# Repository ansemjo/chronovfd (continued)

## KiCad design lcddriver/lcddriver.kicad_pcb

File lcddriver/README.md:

# lcddriver

This isn't entirely my own design and is instead heavily based on David Johnson-Davies' ["Low-Power LCD Clock" design on Technoblogy](http://www.technoblogy.com/show?19K8) (archived: [page](https://archive.ph/uYsL3), [firmware](https://archive.ph/4itl0)). This was created shortly after the `vfddriver` v2 and was meant to use the same physical format and I2C protocol to be a drop-in replacement. In practice, I haven't really bothered to write a separate firmware and used it as a standalone clock with David's firmware instead.

It just needed a few small modifications from the original:

* Only `PE0` is connected to the display's `COM`. `PE1` is used for an LED and if you use the firmware as-is, you'll have a constantly flashing LED.

* I used an **AVR32DB48** and apparently (?) it lacks some of the ADC stuff necessary to read its own voltage? So I just removed `ADCSetup()`, `DisplayVoltage()` and the references to it.

* Additionally, I removed the temperature display and reduced the blinking frequency of the colon by to 2 Hz.

There is also an inverted variant of the firmware, for when you want to operate the clock rotated by 180°, since the LCD segments are rotationally symmetric but the viewing angle is better from one side.

### Compile

The firmware is in `technoblogy-clock-firmware/`.

The chip [is supported](https://docs.platformio.org/en/latest/boards/atmelmegaavr/AVR32DB48.html) by PlatformIO but back when I tried this, I couldn't get it to work. I got either `Error: Unknown board ID 'AVR32DB48'` or `Error: This board doesn't support Arduino framework!`. Therefore I used the method that David used and installed the [DxCore](https://github.com/SpenceKonde/DxCore) in the Arduino IDE, which I then used to compile the firmware instead.

### Flashing

For some reason the Arduino GUI couldn't directly flash my chip. Probably something about a wrong Python version. I manually installed [`pymcuprog`](https://pypi.org/project/pymcuprog/) in a Python 3.9.12 environment and used:

```
pymcuprog write -d avr32db48 -t uart -u /dev/ttyUSB1 -f lcdclock.ino.hex
```

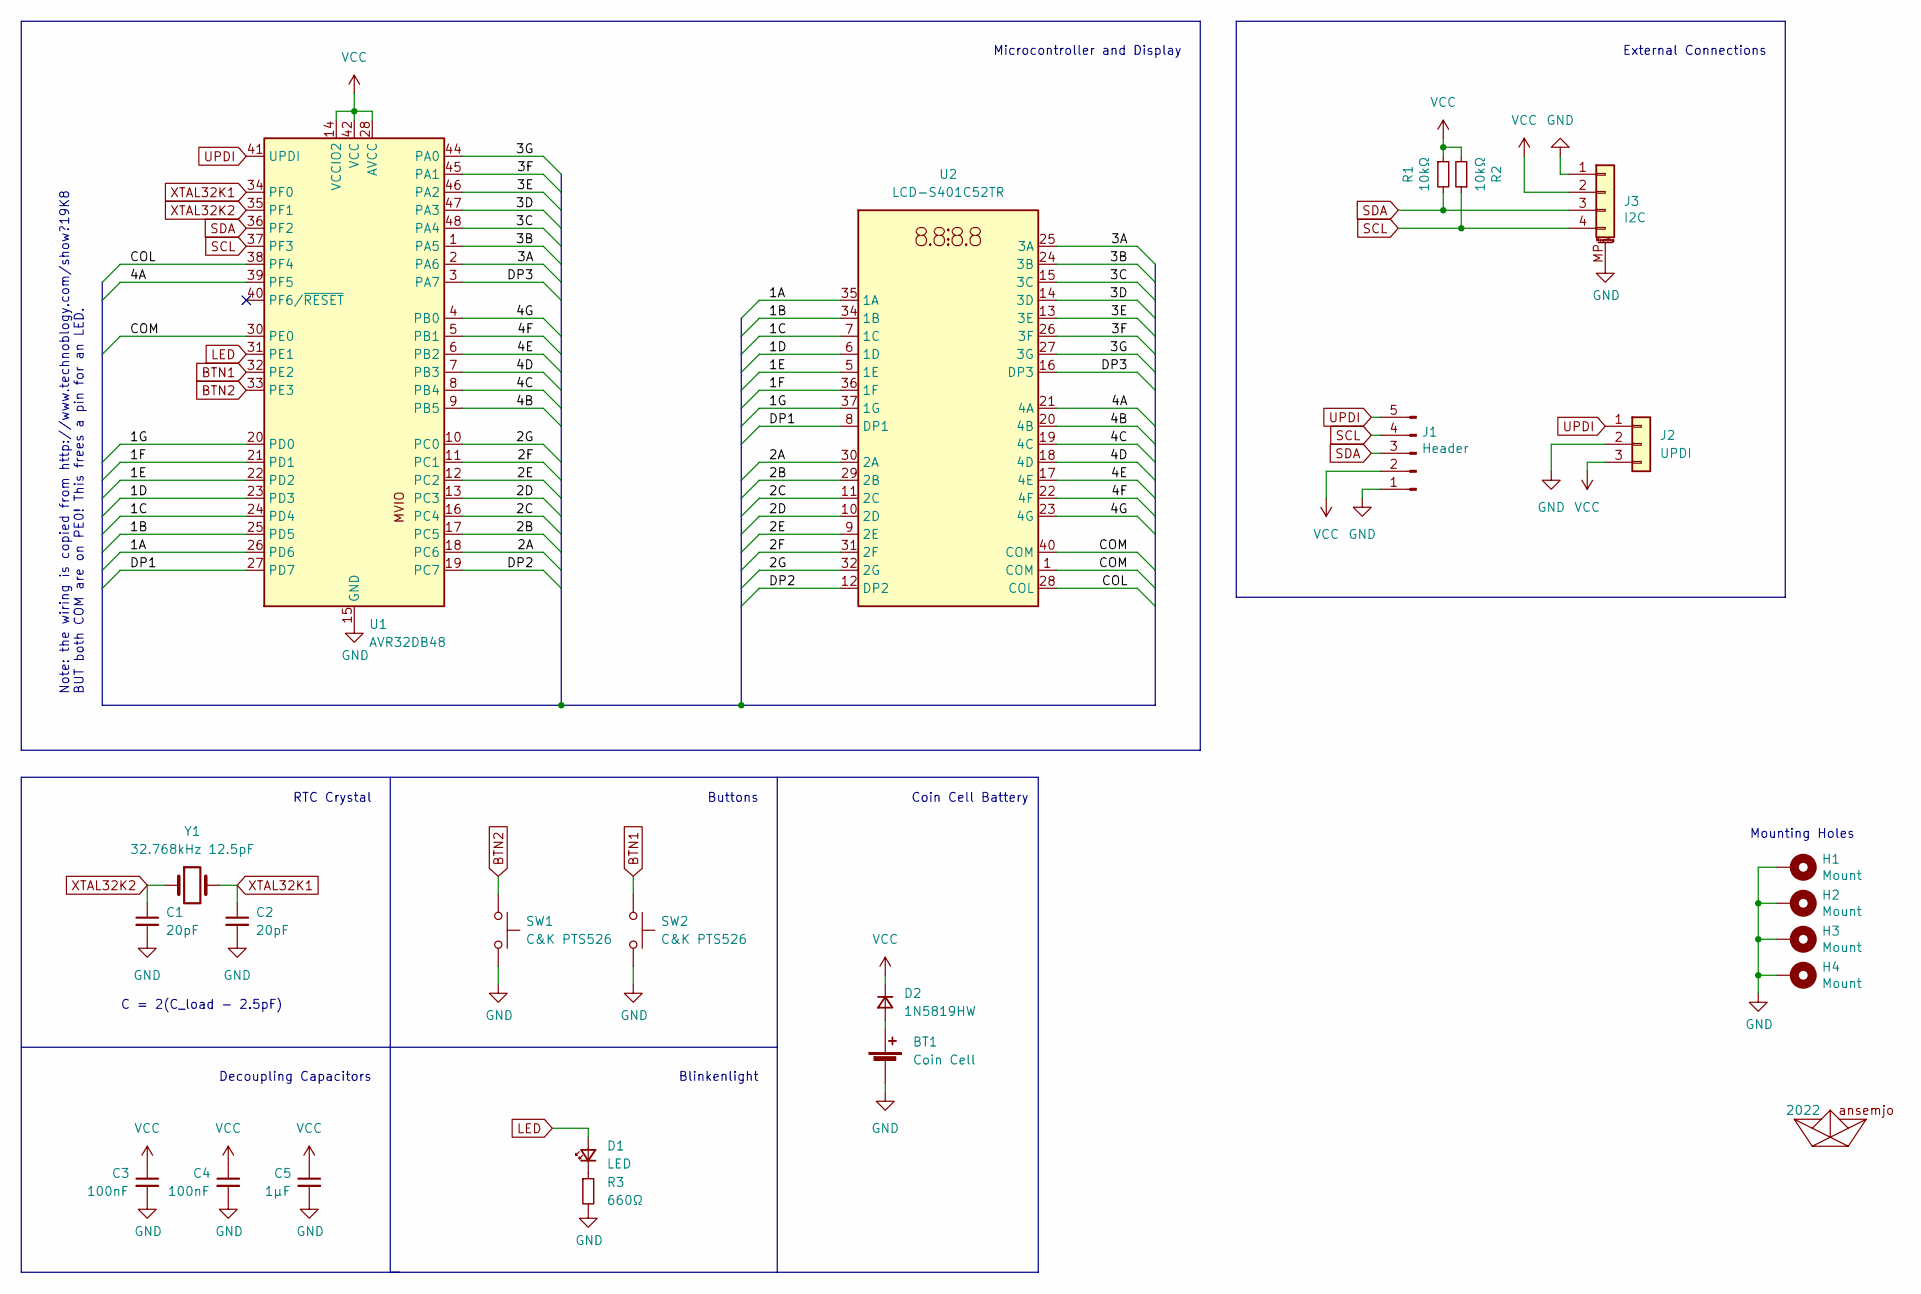
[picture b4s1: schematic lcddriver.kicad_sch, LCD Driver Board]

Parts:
A1: 2022; ahoi
BT1: Coin Cell; BatteryHolder_Keystone_3034_1x20mm
C1, C2: 20pF; C_0603_1608Metric_Pad1.08x0.95mm_HandSolder
C3, C4: 100nF; C_0805_2012Metric_Pad1.18x1.45mm_HandSolder; MPN UMK212BBJ475KG-T; Digi-Key PN 587-5485-1-ND
C5: 1µF; C_0805_2012Metric_Pad1.18x1.45mm_HandSolder; MPN UMK212BBJ475KG-T; Digi-Key PN 587-5485-1-ND
D1: LED; LED_0805_2012Metric_Pad1.15x1.40mm_HandSolder
D2: 1N5819HW; D_SOD-123
H1, H2, H3, H4: Mount; MountingHole_2.7mm_M2.5_Pad
J1: Header; PinHeader_1x05_P2.54mm_Vertical; MPN PREC040DBAN-M71RC; Digi-Key PN S2112EC-40-ND
J2: UPDI; UPDI_PogoProg
J3: I2C; JST_SH_SM04B-SRSS-TB_1x04-1MP_P1.00mm_Horizontal
R1, R2: 10kΩ; R_0805_2012Metric_Pad1.20x1.40mm_HandSolder; MPN RC0805FR-0710KL; Digi-Key PN 311-10.0KCRCT-ND
R3: 660Ω; R_0805_2012Metric_Pad1.20x1.40mm_HandSolder
SW1, SW2: C&K PTS526; SW_PTS526_SM08_SMTR2_LFS
U1: AVR32DB48; TQFP-48_7x7mm_P0.5mm
U2: LCD-S401C52TR; DE119-XX-XX
Y1: 32.768kHz 12.5pF; Crystal_SMD_3215-2Pin_3.2x1.5mm

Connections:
/1A: U1.26 (PD6), U2.35 (1A)
/1B: U1.25 (PD5), U2.34 (1B)
/1C: U1.24 (PD4), U2.7 (1C)
/1D: U1.23 (PD3), U2.6 (1D)
/1E: U1.22 (PD2), U2.5 (1E)
/1F: U1.21 (PD1), U2.36 (1F)
/1G: U1.20 (PD0), U2.37 (1G)
/2A: U1.18 (PC6), U2.30 (2A)
/2B: U1.17 (PC5), U2.29 (2B)
/2C: U1.16 (PC4), U2.11 (2C)
/2D: U1.13 (PC3), U2.10 (2D)
/2E: U1.12 (PC2), U2.9 (2E)
/2F: U1.11 (PC1), U2.31 (2F)
/2G: U1.10 (PC0), U2.32 (2G)
/3A: U1.2 (PA6), U2.25 (3A)
/3B: U1.1 (PA5), U2.24 (3B)
/3C: U1.48 (PA4), U2.15 (3C)
/3D: U1.47 (PA3), U2.14 (3D)
/3E: U1.46 (PA2), U2.13 (3E)
/3F: U1.45 (PA1), U2.26 (3F)
/3G: U1.44 (PA0), U2.27 (3G)
/4A: U1.39 (PF5), U2.21 (4A)
/4B: U1.9 (PB5), U2.20 (4B)
/4C: U1.8 (PB4), U2.19 (4C)
/4D: U1.7 (PB3), U2.18 (4D)
/4E: U1.6 (PB2), U2.17 (4E)
/4F: U1.5 (PB1), U2.22 (4F)
/4G: U1.4 (PB0), U2.23 (4G)
/COL: U1.38 (PF4), U2.28 (COL)
/COM: U1.30 (PE0), U2.1 (COM), U2.40 (COM)
/DP1: U1.27 (PD7), U2.8 (DP1)
/DP2: U1.19 (PC7), U2.12 (DP2)
/DP3: U1.3 (PA7), U2.16 (DP3)
BTN1: SW2.1, U1.32 (PE2)
BTN2: SW1.1, U1.33 (PE3)
GND: BT1.2 (-), C1.2, C2.2, C3.2, C4.2, C5.2, H1.1, H2.1, H3.1, H4.1, J1.1, J2.2, J3.1, J3.MP (MountPin), R3.2, SW1.2, SW2.2, U1.15 (GND), U1.29 (GND), U1.43 (GND)
LED: D1.2 (A), U1.31 (PE1)
unnamed: BT1.1 (+), D2.2 (A)
unnamed: D1.1 (K), R3.1
SCL: J1.4, J3.4, R2.1, U1.37 (PF3)
SDA: J1.3, J3.3, R1.2, U1.36 (PF2)
UPDI: J1.5, J2.1, U1.41 (UPDI)
XTAL32K1: C2.1, U1.34 (PF0), Y1.2
XTAL32K2: C1.1, U1.35 (PF1), Y1.1

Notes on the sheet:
Decoupling Capacitors
Buttons
RTC Crystal
C = 2(C_load - 2.5pF)
Blinkenlight
Coin Cell Battery
Note: the wiring is copied from http://www.technoblogy.com/show?19K8 BUT both COM are on PE0! This frees a pin for an LED.
Microcontroller and Display
Mounting Holes
External Connections

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
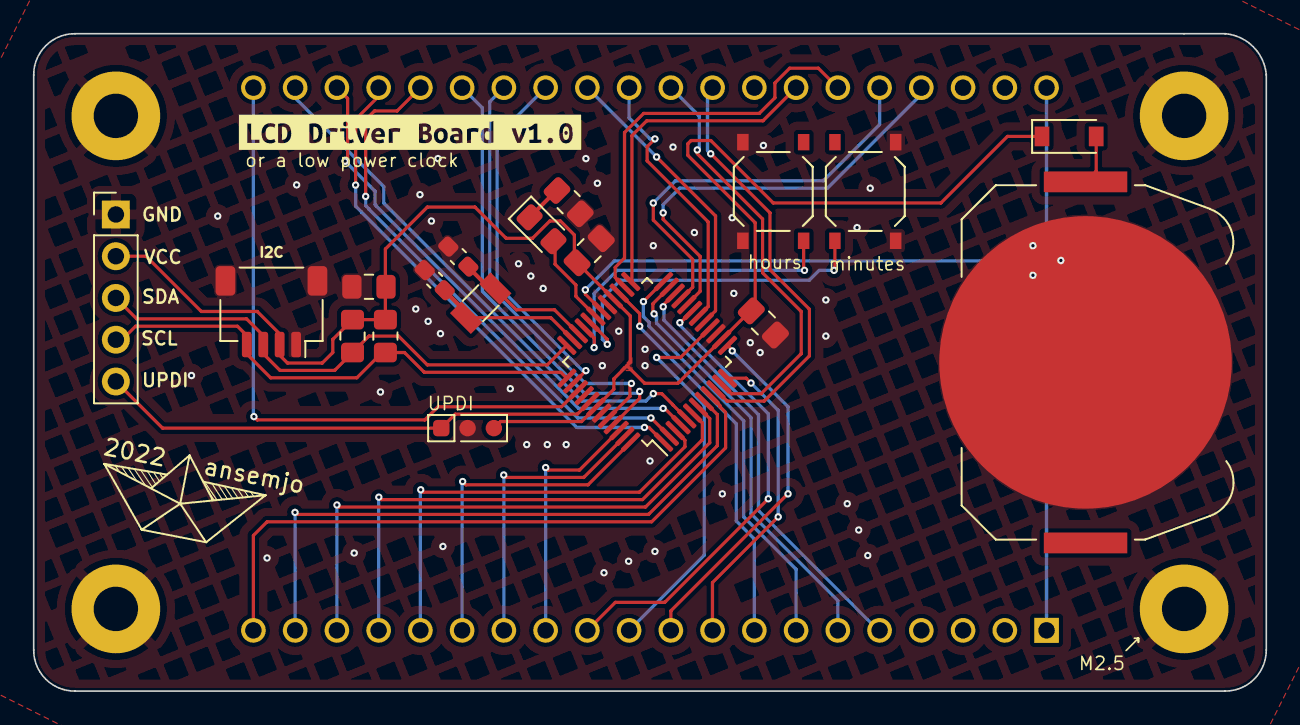
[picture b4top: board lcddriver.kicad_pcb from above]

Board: 2 copper layers, 75.0 x 40.0 mm, 25 parts (1 on the bottom side), 45 nets.

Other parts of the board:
kibuzzard-6311A385: G***; kibuzzard-6311A385

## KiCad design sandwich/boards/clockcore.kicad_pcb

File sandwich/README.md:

# chronovfd

~~ *a vacuum-flourescent display clock project* ~~

The first prototype of this clock was built completely on protoboard and can be
seen on [my Twitter](https://twitter.com/ansemjo/status/1235315817937596424).

This has become my first somewhat complex hardware project and as of now I have
assembled multiple printed circuit boards for the "display driver" and the
"clock core". After fiddling with Espressif's development framework for a while
the assembled hardware now actually works as a clock with internet time
synchronization. :)

You'll find:

* some initial research and ressources on the topic in `research/`
* [hardware](#hardware) files in `hardware/`
* the [firmware](#firmware) in a PlatformIO project in `firmware/`

# Hardware

As mentioned above the final assembly consists of two sandwiched boards:

* [VFD Driver](#vfd-driver-board)
* [Clock Core](#clock-core)

The boards were designed with KiCad version 5.1.6.

The bill-of-materials files contain Digi-Key part numbers, so you can easily
import all parts into your cart. Only the IVL2-7/5 display itself needs to be
sourced elsewhere but there are plenty on [eBay](https://www.ebay.com/sch/i.html?_nkw=ivl2-7%2F5).

Both boards can be screwed together e.g. with 11 mm M2.5 standoffs between
them. I have found some that are marketed as a "Raspberry Pi assembly kit" that
fit well.

### Errata

Sometimes things go wrong .. these are known errors and how to fix them:

* [Rev1.0: Fix the ambient light sensor photodiode](hardware/errata/rev1.0-photodiode/erratum-photodiode.md)

## VFD Driver Board

The VFD driver board is basically a power supply and a simple shift register
with a high-voltage capable output side. I used Rolo's *Universal VFD PSU*
design from [this EEVblog forum post](https://www.eevblog.com/forum/projects/showing-my-vfd-psu/).
The original [schematics](research/universal-vfd-psu/schematic_r2.1.pdf) and
a few pictures are mirrored in `research/universal-vfd-psu/`.

It can be used standalone but there is no logic on the board, so you'll have
to implement time multiplexing for the digits yourself. See the
[Microchip HV5812 datasheet](http://ww1.microchip.com/downloads/en/DeviceDoc/20005629A.pdf)
for more information. The gist is:

* supply regulated 5V power on `GND` / `5V`
* data is transmitted over `clock` and `data` with SPI mode 0 transactions at 5 MHz
* the output pin numbers are listed with their segment or grid function on the silkscreen
* toggle the `strobe` pin `HIGH` to latch the data to the high voltage outputs
* pulling the `filShdn` pin `HIGH` disables the filament supply
* pulling the `hvShdn` pin `LOW` disabled the high-voltage supply
* when the shutdown pins are left floating / in high-Z state, they are pulled active internally, so the display is "on"
* PWM dimming the brigthness with the filament shutdown pin is possible

### Design files

| type | file |
| ---- | ---- |
| kicad project | `hardware/vfddriver.pro` |
| schematic | [`hardware/vfddriver.pdf`](https://github.com/ansemjo/chronovfd/raw/master/hardware/vfddriver.pdf) |
| bill of materials | [`hardware/vfddriver_bom.csv`](hardware/vfddriver_bom.csv) |
| interactive bom | [`hardware/vfddriver_ibom.html`](https://raw.githack.com/ansemjo/chronovfd/master/hardware/vfddriver_ibom.html) |

### Images

## Clock Core

The Clock Core board is the control logic for this clock project. If you look
at the bill of materials it is a relatively expensive board for what it's
supposed to do but I wanted to experiment with some of these components. On
this board there are:

* an Espressif `ESP32-WROOM-32` module, which has WiFi and Bluetooth connectivity
* a USB 2.0 Type-C receptacle for power and data with relatively good input protections and a 3.3V linear regulator
* an FTDI `FT231XS` with an auto-reset circuit providing a serial programming and communication interface to the ESP32
* a Maxim `DS1338Z-33+` RTC with a crystal, which is connected to the ESP32 over I²C and has a coin cell battery backup
* a Maxim `DS18B20U` temperature sensor with a OneWire interface
* a footprint for a photodiode to sense ambient light levels
* a Texas Instruments `SN74HCT245PWR` level shifter to provide the correct logic levels to the VFD driver board
* a PWR and a USR LED for that blinkenlights, the PWR LED can be disabled by cutting a solder jumper
* a 10-pin 1.27mm JTAG header for the ESP32

### Design files

| type | file |
| ---- | ---- |
| kicad project | `hardware/clockcore.pro` |
| schematic | [`hardware/clockcore.pdf`](https://github.com/ansemjo/chronovfd/raw/master/hardware/clockcore.pdf) |
| bill of materials | [`hardware/clockcore_bom.csv`](hardware/clockcore_bom.csv) |
| interactive bom | [`hardware/clockcore_ibom.html`](https://raw.githack.com/ansemjo/chronovfd/master/hardware/clockcore_ibom.html) |

### Images

# Firmware

The firmware is kept in a PlatformIO project. So – if you have `platformio`
already installed – all you need to do is connect the Clock Core via USB and run:

    pio run -t upload

Generally, this board is compatible with most ESP32 devkit configurations. I'm
using a custom board definition mainly to get faster upload speeds, which the
onboard FTDI FT231X can handle. For new projects you may use `pio init -b esp32dev`.

After flashing the firmware, the board starts in **provisioning mode** and you'll
see the word `Prov` blink on the display. Use the
[ESP BLE Provisioning](https://play.google.com/store/apps/details?id=com.espressif.provble)
app to connect and provision your WiFi credentials.

**Note:** I haven't configured a *proof-of-posession* in the firmware, so you
must disable *Encrypted Device Communication* in the app settings first. If you
want to encrypt the provisioning step, look into `wireless_provision()` in
`src/wireless.c`.

Afterwards, the chip will connect to the internet and attempt to synchronize the
time. This will be written to the RTC, which will keep the time as long as an
RTC backup battery is present. If upon poweron the last synchronization is more
than two hours ago, the clock will be synchronized once immediately. Otherwise
it runs on a schedule every night at 05:00. See `src/realtimeclock.c` if you
want to change that. You should probably also fix the timezone if you're not
in the "Europe/Berlin" zone. That is set in `app_main()` with a call to `setenv()`.

# LICENSE

Unless otherwise noted in the file (`ds1307.*`, `i2cdev.*`) the firmware is licensed
under an MIT license, which can be found in [LICENSE](LICENSE).

The hardware project is licensed under a CERN Open Hardware Licence Version 2 -
Permissive, which can be found in [hardware/LICENSE](hardware/LICENSE).

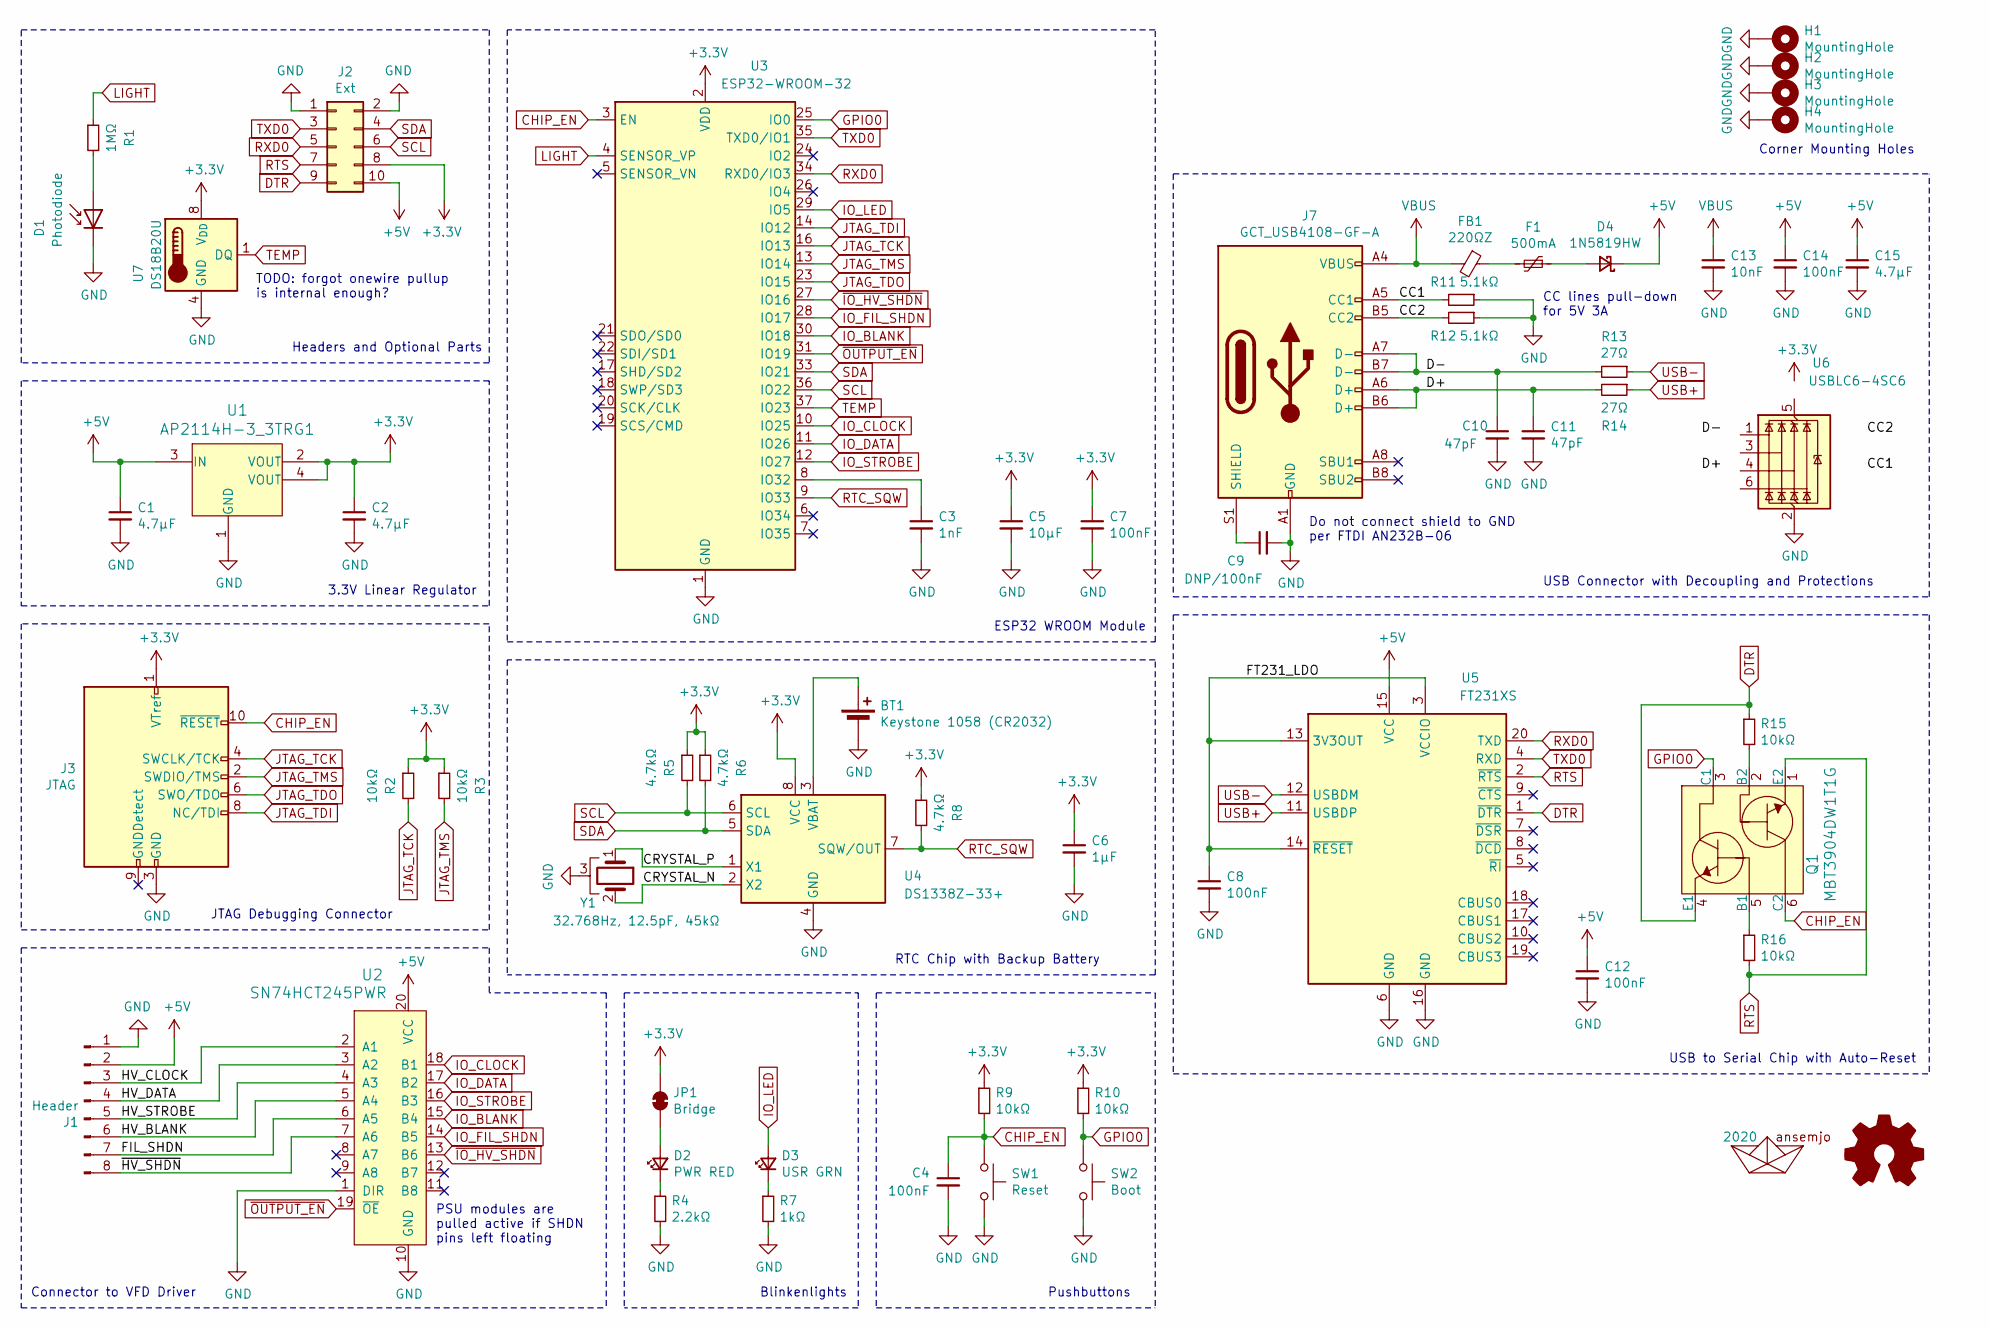
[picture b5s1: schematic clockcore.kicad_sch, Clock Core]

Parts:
A1: 2020; AHOI
A2: Logo_Open_Hardware_Small; OSHW-Symbol_6.7x6mm_SilkScreen
BT1: Keystone 1058 (CR2032); BatteryHolder_Keystone_1058_1x2032; MPN 1058; Digi-Key_PN 36-1058-ND
C1, C2, C15: 4.7µF; C_0805_2012Metric_Pad1.15x1.40mm_HandSolder; MPN CL21A475KAQNNNE; Digi-Key_PN 1276-1244-1-ND
C3: 1nF; C_0805_2012Metric_Pad1.15x1.40mm_HandSolder; MPN CL21B102KBANNNC; Digi-Key_PN 1276-1020-1-ND
C4, C7, C8, C12, C14: 100nF; C_0805_2012Metric_Pad1.15x1.40mm_HandSolder; MPN CL21B104KACNNNC; Digi-Key_PN 1276-1099-1-ND
C5: 10µF; C_0805_2012Metric_Pad1.15x1.40mm_HandSolder; MPN CL21A106KOQNNNE; Digi-Key_PN 1276-1096-1-ND
C6: 1µF; C_0805_2012Metric_Pad1.15x1.40mm_HandSolder; MPN CL21B105KAFNNNG; Digi-Key_PN 1276-6469-1-ND
C9: DNP/100nF; C_0805_2012Metric_Pad1.15x1.40mm_HandSolder; MPN CL21B104KACNNNC; Digi-Key_PN 1276-1099-1-ND
C10, C11: 47pF; C_0805_2012Metric_Pad1.15x1.40mm_HandSolder; MPN CC0805JRNPO9BN470; Digi-Key_PN 311-1107-1-ND
C13: 10nF; C_0805_2012Metric_Pad1.15x1.40mm_HandSolder; MPN CC0805KRX7R9BB103; Digi-Key_PN 311-1136-1-ND
D1: Photodiode; D_1206_3216Metric_Castellated; MPN VEMD1060X01; Digi-Key_PN VEMD1060X01CT-ND
D2: PWR RED; LED_0805_2012Metric_Pad1.15x1.40mm_HandSolder; MPN 150080SS75000; Digi-Key_PN 732-4985-1-ND
D3: USR GRN; LED_0805_2012Metric_Pad1.15x1.40mm_HandSolder; MPN 150080VS75000; Digi-Key_PN 732-4986-1-ND
D4: 1N5819HW; D_SOD-123; MPN 1N5819HW-7-F; Digi-Key_PN 1N5819HW-FDICT-ND
F1: 500mA; Fuse_1206_3216Metric_Pad1.42x1.75mm_HandSolder; MPN 0ZCJ0050FF2G; Digi-Key_PN 507-1802-1-ND
FB1: 220ΩZ; L_0805_2012Metric_Pad1.15x1.40mm_HandSolder; MPN BLM21PG221SZ1D; Digi-Key_PN 490-16661-1-ND
H1, H2, H3, H4: MountingHole; MountingHole_2.7mm_M2.5_Pad
J1: Header; PinSocket_1x08_P2.54mm_Vertical; MPN PPTC081LFBN-RC; Digi-Key_PN S7006-ND
J2: Ext; PinHeader_2x05_P2.54mm_Vertical; MPN PRPC040DAAN-RC; Digi-Key_PN S2011EC-40-ND
J3: JTAG; JTAG_2x05_P1.27mm_Vertical_SMD; MPN 20021121-00010C4LF; Digi-Key_PN 609-3695-6-ND
J7: GCT_USB4108-GF-A; USB_C_Receptacle_HRO_TYPE-C-31-M-12; MPN USB4105-GF-A; Digi-Key_PN 2073-USB4105-GF-ACT-ND
JP1: Bridge; SolderJumper-2_P1.3mm_Bridged_RoundedPad1.0x1.5mm
Q1: MBT3904DW1T1G; SOT-363; MPN MBT3904DW1T1G; Digi-Key_PN MBT3904DW1T1GOSCT-ND
R1: 1MΩ; R_0805_2012Metric_Pad1.15x1.40mm_HandSolder; MPN RC0805FR-071ML; Digi-Key_PN 311-1.00MCRCT-ND
R2, R3, R9, R10, R15, R16: 10kΩ; R_0805_2012Metric_Pad1.15x1.40mm_HandSolder; MPN RC0805FR-0710KL; Digi-Key_PN 311-10.0KCRCT-ND
R4: 2.2kΩ; R_0805_2012Metric_Pad1.15x1.40mm_HandSolder; MPN RC0805FR-072K2L; Digi-Key_PN 311-2.20KCRCT-ND
R5, R6, R8: 4.7kΩ; R_0805_2012Metric_Pad1.15x1.40mm_HandSolder; MPN RC0805FR-074K7L; Digi-Key_PN 311-4.70KCRCT-ND
R7: 1kΩ; R_0805_2012Metric_Pad1.15x1.40mm_HandSolder; MPN RC0805FR-071KL; Digi-Key_PN 311-1.00KCRCT-ND
R11, R12: 5.1kΩ; R_0805_2012Metric_Pad1.15x1.40mm_HandSolder; MPN RC0805JR-075K1L; Digi-Key_PN 311-5.1KARCT-ND
R13, R14: 27Ω; R_0805_2012Metric_Pad1.15x1.40mm_HandSolder; MPN RC0805FR-0727RL; Digi-Key_PN 311-27.0CRCT-ND
SW1: Reset; SW_PTS526_SM08_SMTR2_LFS; MPN PTS526 SK15 SMTR2 LFS; Digi-Key_PN CKN12221-1-ND
SW2: Boot; SW_PTS526_SM08_SMTR2_LFS; MPN PTS526 SK15 SMTR2 LFS; Digi-Key_PN CKN12221-1-ND
U1: AP2114H-3_3TRG1; SOT-223; MPN AP2114H-3.3TRG1; Digi-Key_PN AP2114H-3.3TRG1DICT-ND
U2: ‎SN74HCT245PWR‎; TSSOP-20_4.4x6.5mm_P0.65mm; MPN SN74HCT245PWR; Digi-Key_PN 296-8404-1-ND
U3: ESP32-WROOM-32; MPN ESP32-WROOM-32E (8MB); Digi-Key_PN 1965-ESP32-WROOM-32E(8MBFLASH)CT-ND
U4: DS1338Z-33+; SOIC-8_3.9x4.9mm_P1.27mm; MPN DS1338Z-33+T&R; Digi-Key_PN DS1338Z-33+T&RCT-ND
U5: FT231XS; SSOP-20_3.9x8.7mm_P0.635mm; MPN FT231XS-R; Digi-Key_PN 768-1129-1-ND
U6: USBLC6-4SC6; SOT-23-6; MPN USBLC6-4SC6; Digi-Key_PN 497-4492-1-ND
U7: DS18B20U; MSOP-8_3x3mm_P0.65mm; MPN DS18B20U+T&R; Digi-Key_PN DS18B20U+T&RCT-ND
Y1: 32.768Hz, 12.5pF, 45kΩ; Crystal_SMD_MicroCrystal_MS1V-T1K; MPN ECS-.327-12.5-13FLX-C; Digi-Key_PN XC1911CT-ND

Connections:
+3V3: C2.1, C5.1, C6.1, C7.1, J2.8, J3.1 (VTref), JP1.1 (A), R2.1, R3.1, R5.1, R6.1, R8.1, R9.1, R10.1, U1.2 (VOUT), U1.4 (VOUT), U3.2 (VDD), U4.8 (VCC), U6.5 (VBUS), U7.8 (V_{DD})
+5V: C1.1, C12.1, C14.1, C15.1, D4.1 (K), J1.2, J2.10, U1.3 (IN), U2.20 (VCC), U5.15 (VCC)
/CC1: J7.A5 (CC1), R11.2, U6.6 (I/O4)
/CC2: J7.B5 (CC2), R12.2, U6.4 (I/O3)
/CRYSTAL_N: U4.2 (X2), Y1.2
/CRYSTAL_P: U4.1 (X1), Y1.1
/D+: C11.1, J7.A6 (D+), J7.B6 (D+), R14.2, U6.3 (I/O2)
/D-: C10.1, J7.A7 (D-), J7.B7 (D-), R13.2, U6.1 (I/O1)
/FIL_SHDN: J1.7, U2.6 (A5)
/FT231_LDO: C8.1, U5.3 (VCCIO), U5.13 (3V3OUT), U5.14 (~RESET)
/HV_BLANK: J1.6, U2.5 (A4)
/HV_CLOCK: J1.3, U2.2 (A1)
/HV_DATA: J1.4, U2.3 (A2)
/HV_STROBE: J1.5, U2.4 (A3)
/~HV_SHDN: J1.8, U2.7 (A6)
CHIP_EN: C4.1, J3.10 (~RESET), Q1.6 (C2), R9.2, SW1.1, U3.3 (EN)
DTR: J2.9, Q1.4 (E1), R15.1, U5.1 (~DTR)
GND: BT1.2 (-), C1.2, C2.2, C3.2, C4.2, C5.2, C6.2, C7.2, C8.2, C9.2, C10.2, C11.2, C12.2, C13.2, C14.2, C15.2, D1.1 (K), H1.1, H2.1, H3.1, H4.1, J1.1, J2.1, J2.2, J3.3 (GND), J3.5 (GND), J7.A1 (GND), J7.A12 (GND), J7.B1 (GND), J7.B12 (GND), R4.2, R7.2, R11.1, R12.1, SW1.2, SW2.2, U1.1 (GND), U2.1 (DIR), U2.10 (GND), U3.1 (GND), U3.15 (GND), U3.38 (GND), U3.39 (GND), U4.4 (GND), U5.6 (GND), U5.16 (GND), U6.2 (GND), U7.4 (GND), Y1.3
GPIO0: Q1.3 (C1), R10.2, SW2.1, U3.25 (IO0)
IO_BLANK: U2.15 (B4), U3.30 (IO18)
IO_CLOCK: U2.18 (B1), U3.10 (IO25)
IO_DATA: U2.17 (B2), U3.11 (IO26)
IO_FIL_SHDN: U2.14 (B5), U3.28 (IO17)
IO_LED: D3.2 (A), U3.29 (IO5)
IO_STROBE: U2.16 (B3), U3.12 (IO27)
JTAG_TCK: J3.4 (SWCLK/TCK), R2.2, U3.16 (IO13)
JTAG_TDI: J3.8 (NC/TDI), U3.14 (IO12)
JTAG_TDO: J3.6 (SWO/TDO), U3.23 (IO15)
JTAG_TMS: J3.2 (SWDIO/TMS), R3.2, U3.13 (IO14)
LIGHT: R1.1, U3.4 (SENSOR_VP)
unnamed: BT1.1 (+), U4.3 (VBAT)
unnamed: C3.1, U3.8 (IO32)
unnamed: C9.1, J7.S1 (SHIELD)
unnamed: D1.2 (A), R1.2
unnamed: D2.1 (K), R4.1
unnamed: D2.2 (A), JP1.2 (B)
unnamed: D3.1 (K), R7.1
unnamed: D4.2 (A), F1.1
unnamed: F1.2, FB1.1
unnamed: Q1.2 (B2), R15.2
unnamed: Q1.5 (B1), R16.1
RTC_SQW: R8.2, U3.9 (IO33), U4.7 (SQW/OUT)
RTS: J2.7, Q1.1 (E2), R16.2, U5.2 (~RTS)
RXD0: J2.5, U3.34 (RXD0/IO3), U5.20 (TXD)
SCL: J2.6, R5.2, U3.36 (IO22), U4.6 (SCL)
SDA: J2.4, R6.2, U3.33 (IO21), U4.5 (SDA)
TEMP: U3.37 (IO23), U7.1 (DQ)
TXD0: J2.3, U3.35 (TXD0/IO1), U5.4 (RXD)
USB+: R14.1, U5.11 (USBDP)
USB-: R13.1, U5.12 (USBDM)
VBUS: C13.1, FB1.2, J7.A4 (VBUS), J7.A9 (VBUS), J7.B4 (VBUS), J7.B9 (VBUS)
~IO_HV_SHDN: U2.13 (B6), U3.27 (IO16)
~OUTPUT_EN: U2.19 (~OE), U3.31 (IO19)

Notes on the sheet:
Blinkenlights
TODO: forgot onewire pullup is internal enough?
Pushbuttons
Do not connect shield to GND per FTDI AN232B-06
Corner Mounting Holes
USB to Serial Chip with Auto-Reset
PSU modules are pulled active if SHDN pins left floating
USB Connector with Decoupling and Protections
Connector to VFD Driver
ESP32 WROOM Module
RTC Chip with Backup Battery
JTAG Debugging Connector
Headers and Optional Parts
3.3V Linear Regulator
CC lines pull-down for 5V 3A

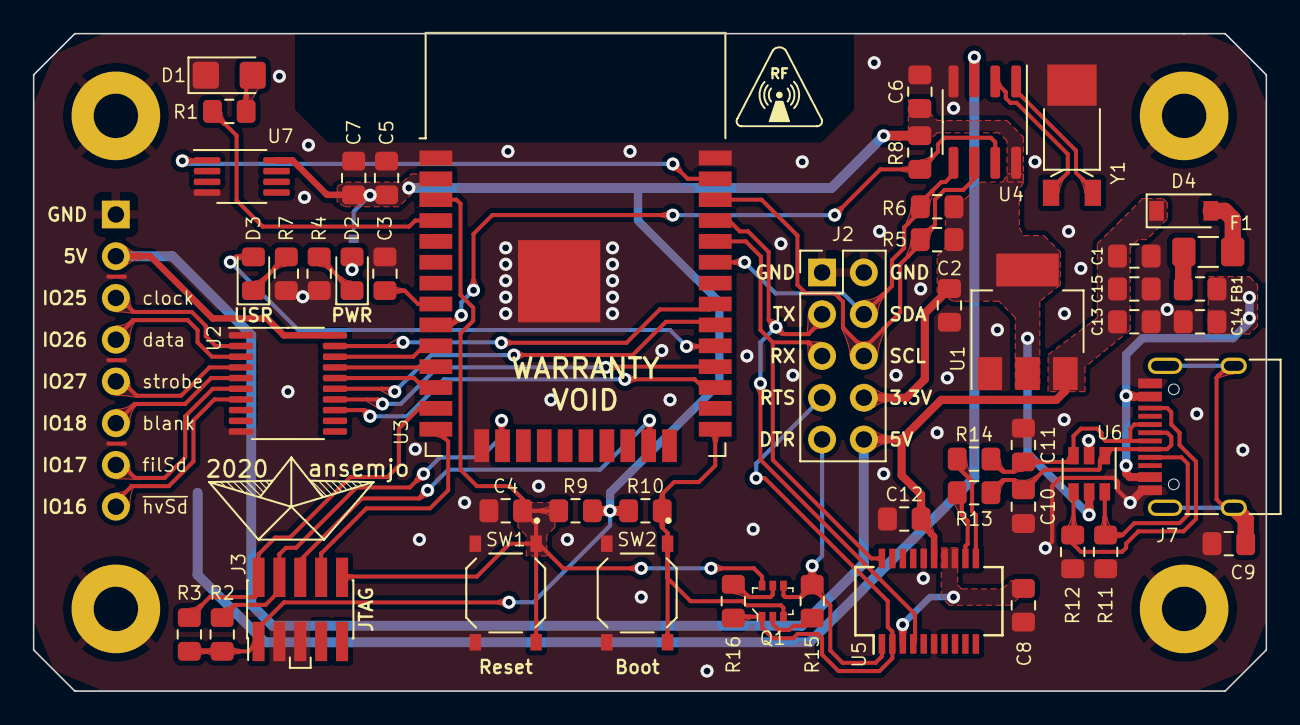
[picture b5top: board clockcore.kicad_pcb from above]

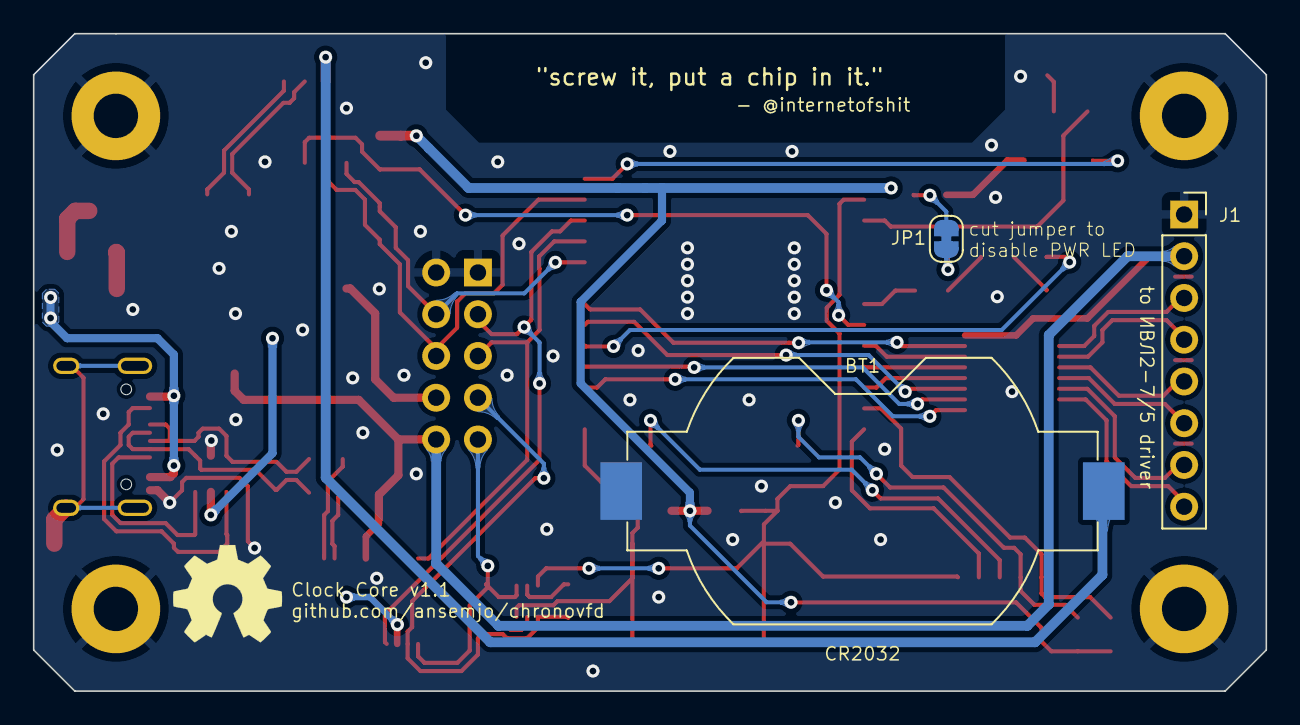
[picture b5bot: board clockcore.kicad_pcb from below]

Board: 2 copper layers, 75.0 x 40.0 mm, 60 parts (4 on the bottom side), 53 nets.

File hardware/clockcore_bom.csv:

References,Value,Quantity Per PCB,Part,Digi-Key_PN,MPN,Manufacturer
BT1,Keystone 1058 (CR2032),1,Battery_Cell,36-1058-ND,1058,Keystone
C4 C7 C8 C12 C14,100nF,5,C_Small,1276-1099-1-ND,CL21B104KACNNNC,Samsung
C13,10nF,1,C_Small,311-1136-1-ND,CC0805KRX7R9BB103,Yageo
C5,10µF,1,C_Small,1276-1096-1-ND,CL21A106KOQNNNE,Samsung
C3,1nF,1,C_Small,1276-1020-1-ND,CL21B102KBANNNC,Samsung
C6,1µF,1,C_Small,1276-6469-1-ND,CL21B105KAFNNNG,Samsung
C1 C2 C15,4.7µF,3,C_Small,1276-1244-1-ND,CL21A475KAQNNNE,Samsung
C10 C11,47pF,2,C_Small,311-1107-1-ND,CC0805JRNPO9BN470,Yageo
C9,DNP/100nF,1,C_Small,1276-1099-1-ND,CL21B104KACNNNC,Samsung
D4,1N5819HW,1,D_Schottky_Small,1N5819HW-FDICT-ND,1N5819HW-7-F,Diodes Inc.
D2,PWR RED,1,LED_Small,732-4985-1-ND,150080SS75000,Würth
D1,Photodiode,1,D_Photo,VEMD1060X01CT-ND,VEMD1060X01,Vishay
D3,USR GRN,1,LED_Small,732-4986-1-ND,150080VS75000,Würth
F1,500mA,1,Polyfuse_Small,507-1802-1-ND,0ZCJ0050FF2G,Bel Fuse
FB1,220ΩZ,1,Ferrite_Bead_Small,490-16661-1-ND,BLM21PG221SZ1D,Murata
J2,Ext,1,Conn_02x05_Odd_Even,S2011EC-40-ND,PRPC040DAAN-RC,Sullins
J7,GCT_USB4108-GF-A,1,USB_C_Receptacle_USB2.0,2073-USB4105-GF-ACT-ND,USB4105-GF-A,GCT
J1,Header,1,Conn_01x08_Male,S7006-ND,PPTC081LFBN-RC,Sullins
J3,JTAG,1,Conn_ARM_JTAG_SWD_10,609-3695-6-ND,20021121-00010C4LF,Amphenol
Q1,MBT3904DW1T1G,1,MBT3904DW1T1G,MBT3904DW1T1GOSCT-ND,MBT3904DW1T1G,ON Semiconductor
R2 R3 R9 R10 R15 R16,10kΩ,6,R_Small,311-10.0KCRCT-ND,RC0805FR-0710KL,Yageo
R1,1MΩ,1,R_Small,311-1.00MCRCT-ND,RC0805FR-071ML,Yageo
R7,1kΩ,1,R_Small,311-1.00KCRCT-ND,RC0805FR-071KL,Yageo
R4,2.2kΩ,1,R_Small,311-2.20KCRCT-ND,RC0805FR-072K2L,Yageo
R13 R14,27Ω,2,R_Small,311-27.0CRCT-ND,RC0805FR-0727RL,Yageo
R5 R6 R8,4.7kΩ,3,R_Small,311-4.70KCRCT-ND,RC0805FR-074K7L,Yageo
R11 R12,5.1kΩ,2,R_Small,311-5.1KARCT-ND,RC0805JR-075K1L,Yageo
SW2,Boot,1,SW_Push,CKN12221-1-ND,PTS526 SK15 SMTR2 LFS,C&K
SW1,Reset,1,SW_Push,CKN12221-1-ND,PTS526 SK15 SMTR2 LFS,C&K
U1,AP2114H-3_3TRG1,1,AP2114H-3_3TRG1,AP2114H-3.3TRG1DICT-ND,AP2114H-3.3TRG1,Diodes Inc.
U4,DS1338Z-33+,1,DS1307ZN+,DS1338Z-33+T&RCT-ND,DS1338Z-33+T&R,Maxim
U7,DS18B20U,1,DS18B20U,DS18B20U+T&RCT-ND,DS18B20U+T&R,Maxim
U3,ESP32-WROOM-32,1,ESP32-WROOM-32,1965-ESP32-WROOM-32E(8MBFLASH)CT-ND,ESP32-WROOM-32E (8MB),Espressif
U5,FT231XS,1,FT231XS,768-1129-1-ND,FT231XS-R,FTDI
U6,USBLC6-4SC6,1,USBLC6-4SC6,497-4492-1-ND,USBLC6-4SC6,ST Microelectronic
U2,‎SN74HCT245PWR‎,1,SN74LVC245AN,296-8404-1-ND,SN74HCT245PWR,Texas Instruments
Y1,"32.768Hz, 12.5pF, 45kΩ",1,Crystal_GND3,XC1911CT-ND,ECS-.327-12.5-13FLX-C,ECS Inc.

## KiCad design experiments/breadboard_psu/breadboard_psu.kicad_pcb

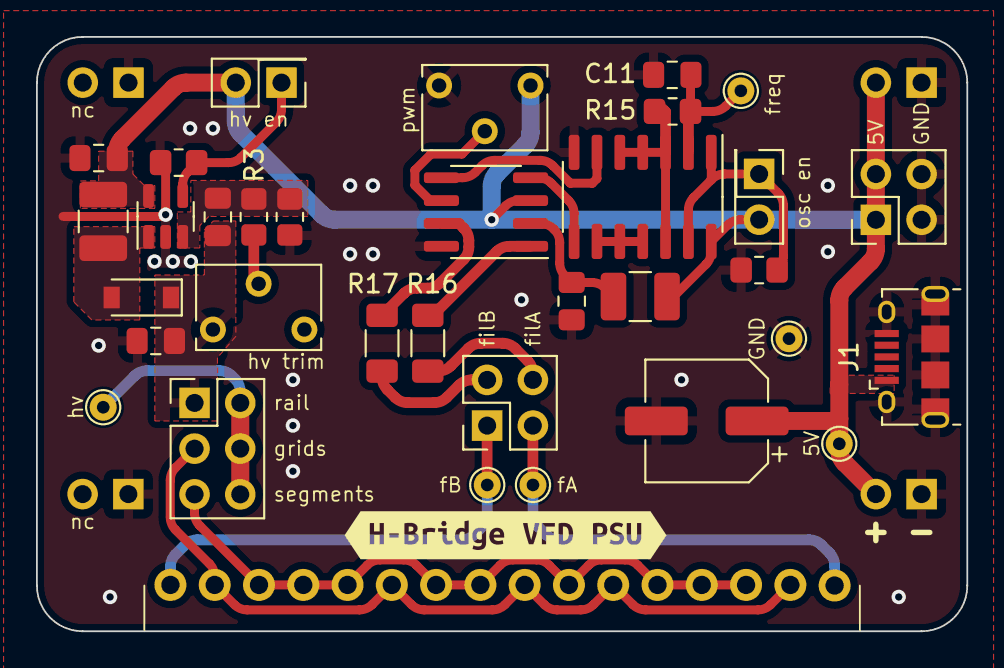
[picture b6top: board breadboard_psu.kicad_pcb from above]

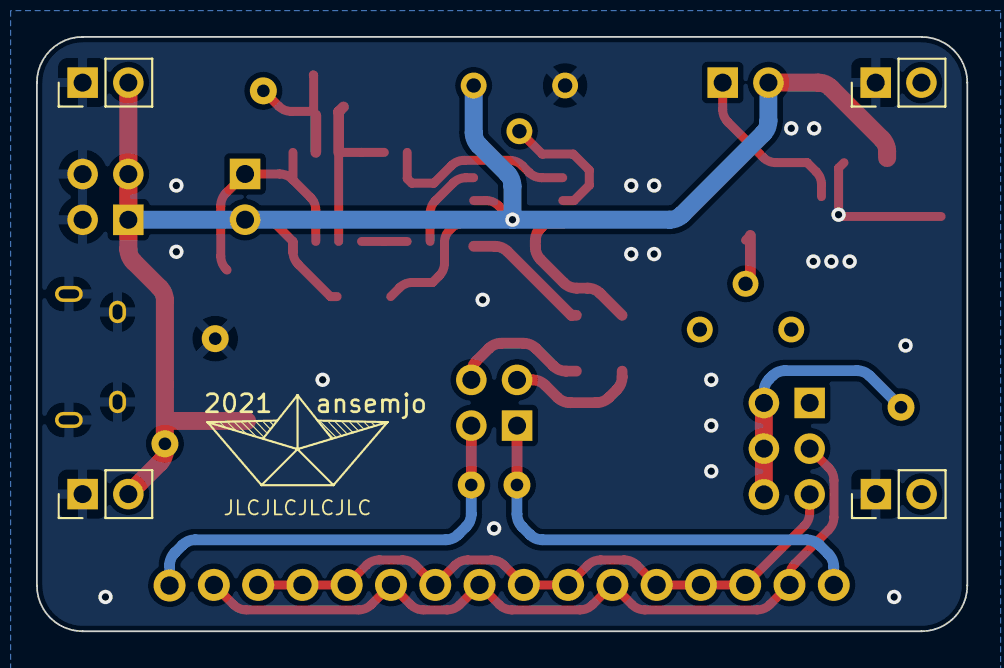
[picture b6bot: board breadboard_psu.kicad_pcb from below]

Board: 2 copper layers, 51.7 x 33.0 mm, 40 parts (5 on the bottom side), 24 nets.

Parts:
A1: 2021; ahoi
C1, C2: 4.7µF; C_0805_2012Metric_Pad1.18x1.45mm_HandSolder
C3: 82pF; C_0805_2012Metric_Pad1.18x1.45mm_HandSolder
C4: 47µF; CP_Elec_6.3x5.9
C11: 10nF; C_0805_2012Metric_Pad1.18x1.45mm_HandSolder
C12: 10µF; C_0805_2012Metric_Pad1.18x1.45mm_HandSolder
D1: 1N5819HW-7-F; D_SOD-123
J1: USB_B_Micro; USB_Micro-B_Amphenol_10118194_Horizontal
J2: PWR Header; PinHeader_2x02_P2.54mm_Vertical
J3: HV Jumper; PinHeader_2x03_P2.54mm_Vertical
J4: Filament Jumper; PinHeader_2x02_P2.54mm_Vertical
J5: Filament EN; PinHeader_2x01_P2.54mm_Vertical
J6: HV EN; PinHeader_2x01_P2.54mm_Vertical
J21, J22: Breadboard Rail; PinHeader_1x02_P2.54mm_Vertical
J31, J32: Breadboard NC; PinHeader_1x02_P2.54mm_Vertical
L1, L2: 10µH; L_1210_3225Metric_Pad1.42x2.65mm_HandSolder
R1: 47kΩ; R_0805_2012Metric_Pad1.20x1.40mm_HandSolder
R2: 13kΩ; R_0805_2012Metric_Pad1.20x1.40mm_HandSolder
R3: 240kΩ; R_0805_2012Metric_Pad1.20x1.40mm_HandSolder
R14, R15: 10kΩ; R_0805_2012Metric_Pad1.20x1.40mm_HandSolder
R16, R17: 10Ω; R_1206_3216Metric_Pad1.30x1.75mm_HandSolder
RV1: Trimmer; Potentiometer_Bourns_3266W_Vertical
RV4: 10kΩ; Potentiometer_Bourns_3266W_Vertical
TP1: 5V; TestPoint_THTPad_D1.5mm_Drill0.7mm
TP2: hv; TestPoint_THTPad_D1.5mm_Drill0.7mm
TP3: freq; TestPoint_THTPad_D1.5mm_Drill0.7mm
TP4: GND; TestPoint_THTPad_D1.5mm_Drill0.7mm
TP11: fB; TestPoint_THTPad_D1.5mm_Drill0.7mm
TP12: fA; TestPoint_THTPad_D1.5mm_Drill0.7mm
U1: 74LS132; SOIC-14_3.9x8.7mm_P1.27mm
U3: LM2733YMF; SOT-23-5
U4: ZXBM5210-S; SOIC-8_3.9x4.9mm_P1.27mm
VFD1: IVL2-5_7; IVL2-7_5-singleSide
kibuzzard-61E14426: G***; kibuzzard-61E14426

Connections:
/5V: C1.1, C4.1, J1.1 (VBUS), J2.1, J2.2, J5.2, J6.2, J21.2, J22.2, L1.1, L2.1, RV1.1, TP1.1, U1.14 (VCC), U3.5 (VIN), U4.3 (VDD)
/FIL_A: J4.3, TP12.1, VFD1.1 (F+)
/FIL_B: J4.1, TP11.1, VFD1.16 (F-)
/FIL_H_A: J4.4, R16.1
/FIL_H_B: J4.2, R17.1
/HV: C2.1, C3.2, D1.1 (K), J3.1, RV4.1
/HV_Grids: J3.3, VFD1.2 (G1), VFD1.6 (G2), VFD1.8 (G3), VFD1.11 (G4), VFD1.15 (G5)
/HV_Jumper: J3.2, J3.4, J3.6, TP2.1
/HV_Segments: J3.5, VFD1.3 (dt), VFD1.4 (g), VFD1.5 (e), VFD1.7 (c), VFD1.9 (db), VFD1.10 (d), VFD1.12 (b), VFD1.13 (f), VFD1.14 (a)
/H_EN: J5.1, R14.1, U1.1, U1.13
GND: C1.2, C2.2, C4.2, C11.2, C12.1, J1.5 (GND), J1.6 (Shield), J2.3, J2.4, J21.1, J22.1, J31.1, J32.1, R1.2, R2.1, R14.2, RV1.3, TP4.1, U1.7 (GND), U3.2 (GND), U4.8 (GND)
unnamed: C3.1, R2.2, R3.2, U3.3 (FB)
unnamed: C11.1, R15.1, TP3.1, U1.2
unnamed: C12.2, L2.2, U4.2 (VM)
unnamed: D1.2 (A), L1.2, U3.1 (SW)
unnamed: J6.1, R1.1, U3.4 (EN)
unnamed: R3.1, RV4.2
unnamed: R15.2, U1.3, U1.4, U1.5, U1.12
unnamed: R16.2, U4.1 (OUT1)
unnamed: R17.2, U4.7 (OUT2)
unnamed: RV1.2, U4.6 (VREF)
unnamed: U1.6, U4.5 (REV)
unnamed: U1.8, U4.4 (FWD)
unnamed: U1.9, U1.10, U1.11
